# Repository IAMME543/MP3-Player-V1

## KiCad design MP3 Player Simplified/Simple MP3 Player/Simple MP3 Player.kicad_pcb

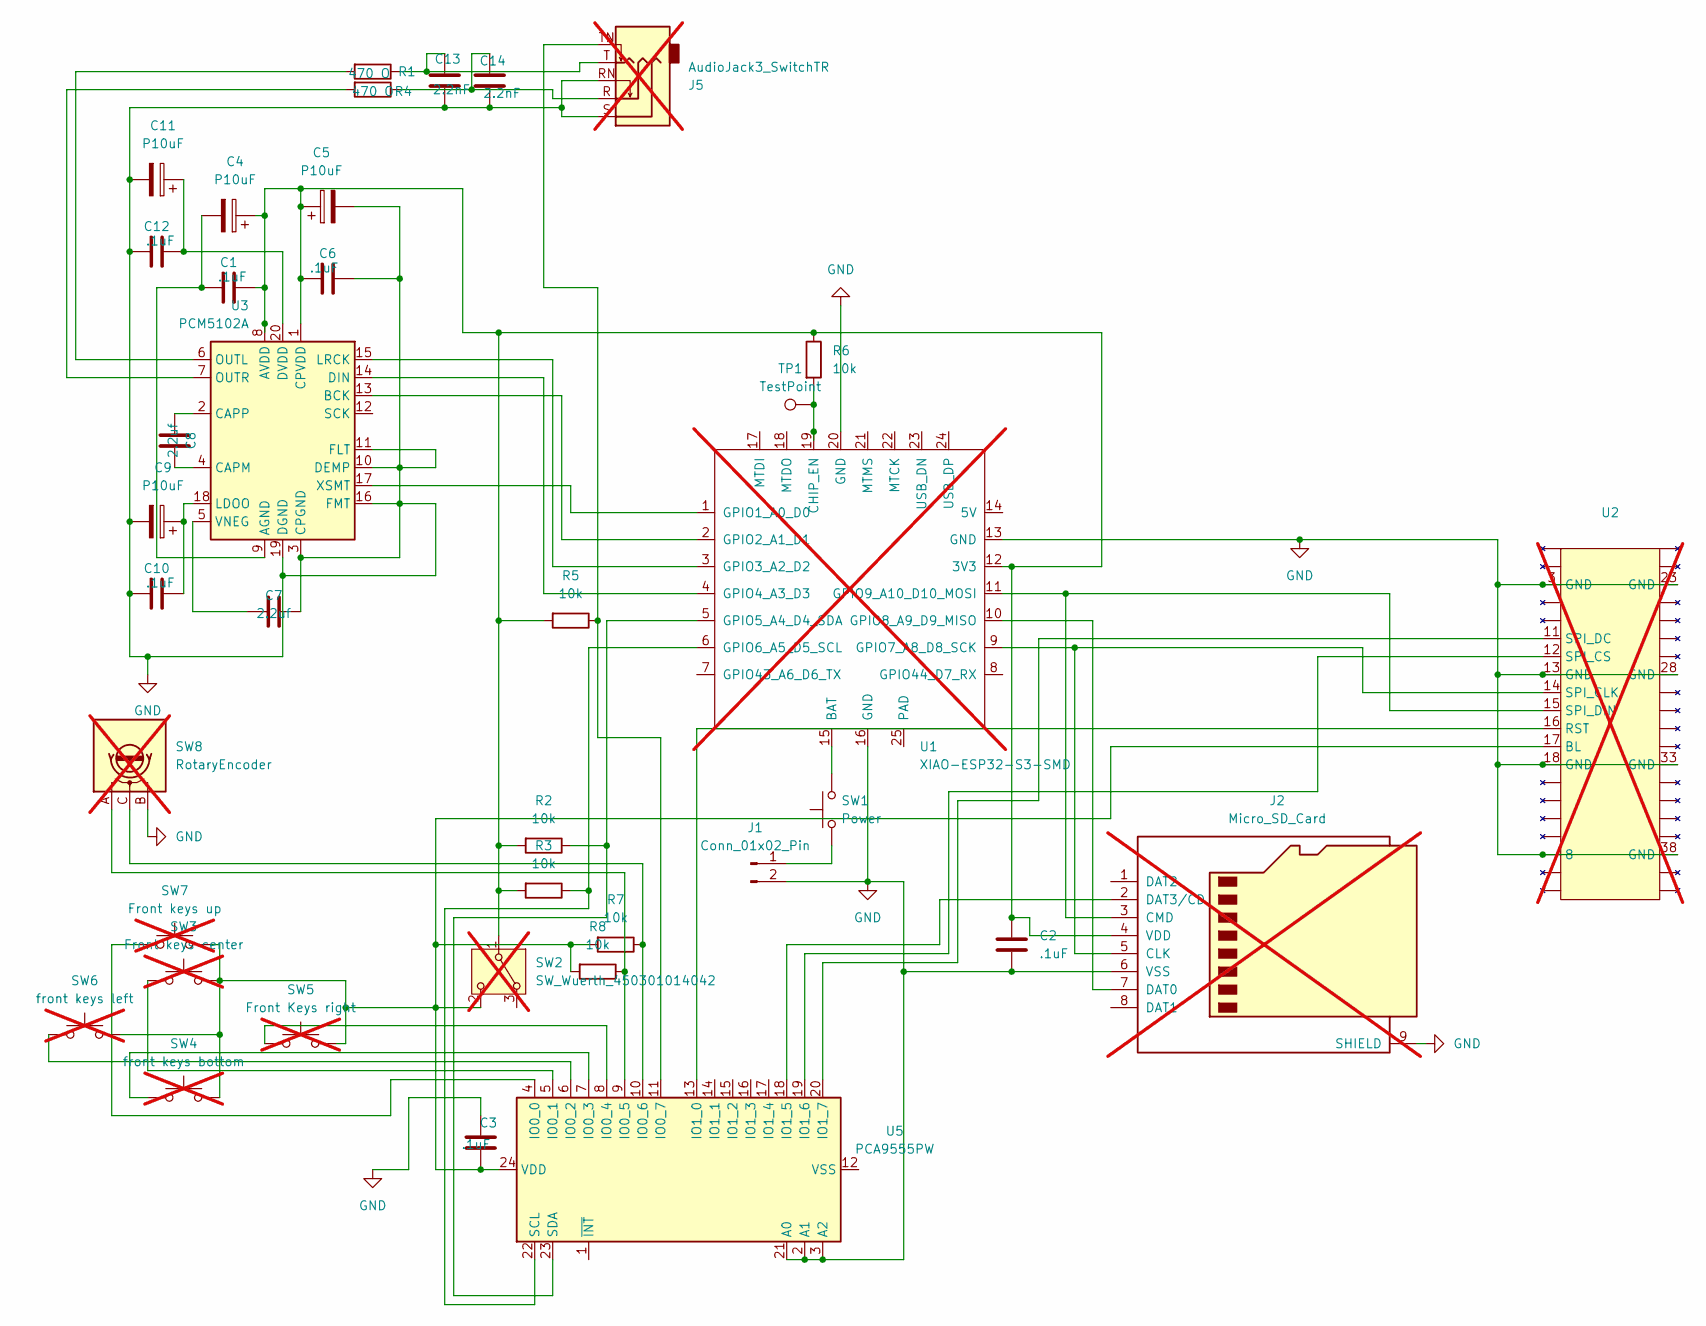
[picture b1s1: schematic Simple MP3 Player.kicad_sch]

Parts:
C1, C2, C3, C6, C10, C12: .1uF; C_0201_0603Metric
C4, C5, C9, C11: P10uF; CP_EIA-1608-08_AVX-J
C7, C8: 2.2uf; C_0201_0603Metric
C13, C14: 2.2nF; C_0201_0603Metric
J1: Conn_01x02_Pin; JST_PH_B2B-PH-K_1x02_P2.00mm_Vertical
J2: Micro_SD_Card; MicroSD Card; not fitted
J5: AudioJack3_SwitchTR; 3.5mm Audio Jack; not fitted
R1, R4: 470 O; R_0201_0603Metric
R2, R3, R5, R6, R7, R8: 10k; R_0201_0603Metric
SW1: Power; SW_Slide-03_Wuerth-WS-SLTV_10x2.5x6.4_P2.54mm
SW2: SW_Wuerth_450301014042; SW_Slide-03_Wuerth-WS-SLTV_10x2.5x6.4_P2.54mm; not fitted
SW3: Front keys center; SW_PUSH-12mm; not fitted
SW4: front keys bottom; SW_PUSH-12mm; not fitted
SW5: Front Keys right; SW_PUSH-12mm; not fitted
SW6: front keys left; SW_PUSH-12mm; not fitted
SW7: Front keys up; SW_PUSH-12mm; not fitted
SW8: RotaryEncoder; RE130F41175F12P; not fitted
TP1: TestPoint
U1: XIAO-ESP32-S3-SMD; XIAO-ESP32C3-SMD; not fitted
U2: Waveshare Pico LCD 2; not fitted
U3: PCM5102A; TSSOP-20_4.4x6.5mm_P0.65mm
U5: PCA9555PW; TSSOP-24_4.4x7.8mm_P0.65mm

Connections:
GND: C2.2, C3.1, C5.2, C6.1, C7.2, C9.2, C10.1, C11.2, C12.1, C13.2, C14.2, J1.2, J2.6 (VSS), J2.9 (SHIELD), J5.RN, J5.S, SW8.B, U1.13 (GND), U1.16 (GND), U1.20 (GND), U2., U2.3 (GND), U2.13 (GND), U2.18 (GND), U2.23 (GND), U2.28 (GND), U2.33 (GND), U2.38 (GND), U3.3 (CPGND), U3.10 (DEMP), U3.11 (FLT), U3.16 (FMT), U3.19 (DGND), U5.2 (A1), U5.3 (A2), U5.21 (A0)
unnamed: C13.1, J5.T, R1.1
unnamed: C14.1, J5.R, R4.1
unnamed: J1.1, SW1.1
unnamed: J2.5 (CLK), U1.9 (GPIO7_A8_D8_SCK), U2.14 (SPI_CLK)
unnamed: J2.3 (CMD), U1.11 (GPIO9_A10_D10_MOSI), U2.15 (SPI_DIN)
unnamed: J2.7 (DAT0), U1.10 (GPIO8_A9_D9_MISO)
unnamed: J2.2 (DAT3/CD), U5.18 (IO1_5)
unnamed: C1.2, C2.1, C4.1, C5.1, C6.2, J2.4 (VDD), R2.2, R3.2, R5.2, R6.1, SW2.1 (B), U1.12 (3V3), U3.1 (CPVDD), U3.8 (AVDD)
unnamed: C3.2, R7.2, R8.2, SW2.2 (C), SW3.2, SW4.2, SW5.2, SW6.2, SW7.2, U2.17 (BL), U5.24 (VDD)
unnamed: SW1.2, U1.15 (BAT)
unnamed: R6.2, TP1.1, U1.19 (CHIP_EN)
unnamed: U1.1 (GPIO1_A0_D0), U3.17 (XSMT)
unnamed: U1.2 (GPIO2_A1_D1), U3.13 (BCK)
unnamed: U1.3 (GPIO3_A2_D2), U3.15 (LRCK)
unnamed: U1.4 (GPIO4_A3_D3), U3.14 (DIN)
unnamed: R2.1, U1.5 (GPIO5_A4_D4_SDA), U5.23 (SDA)
unnamed: R3.1, U1.6 (GPIO6_A5_D5_SCL), U5.22 (SCL)
unnamed: U2.16 (RST), U5.13 (IO1_0)
unnamed: U2.12 (SPI_CS), U5.19 (IO1_6)
unnamed: U2.11 (SPI_DC), U5.20 (IO1_7)
unnamed: C1.1, C4.2, U3.9 (AGND)
unnamed: C8.2, U3.4 (CAPM)
unnamed: C8.1, U3.2 (CAPP)
unnamed: C11.1, C12.2, U3.20 (DVDD)
unnamed: C9.1, C10.2, U3.18 (LDOO)
unnamed: R1.2, U3.6 (OUTL)
unnamed: R4.2, U3.7 (OUTR)
unnamed: C7.1, U3.5 (VNEG)
unnamed: SW7.1, U5.4 (IO0_0)
unnamed: SW3.1, U5.5 (IO0_1)
unnamed: SW6.1, U5.6 (IO0_2)
unnamed: SW4.1, U5.7 (IO0_3)
unnamed: SW5.1, U5.8 (IO0_4)
unnamed: R8.1, SW8.A, U5.9 (IO0_5)
unnamed: R7.1, SW8.C, U5.10 (IO0_6)
unnamed: J5.TN, R5.1, U5.11 (IO0_7)

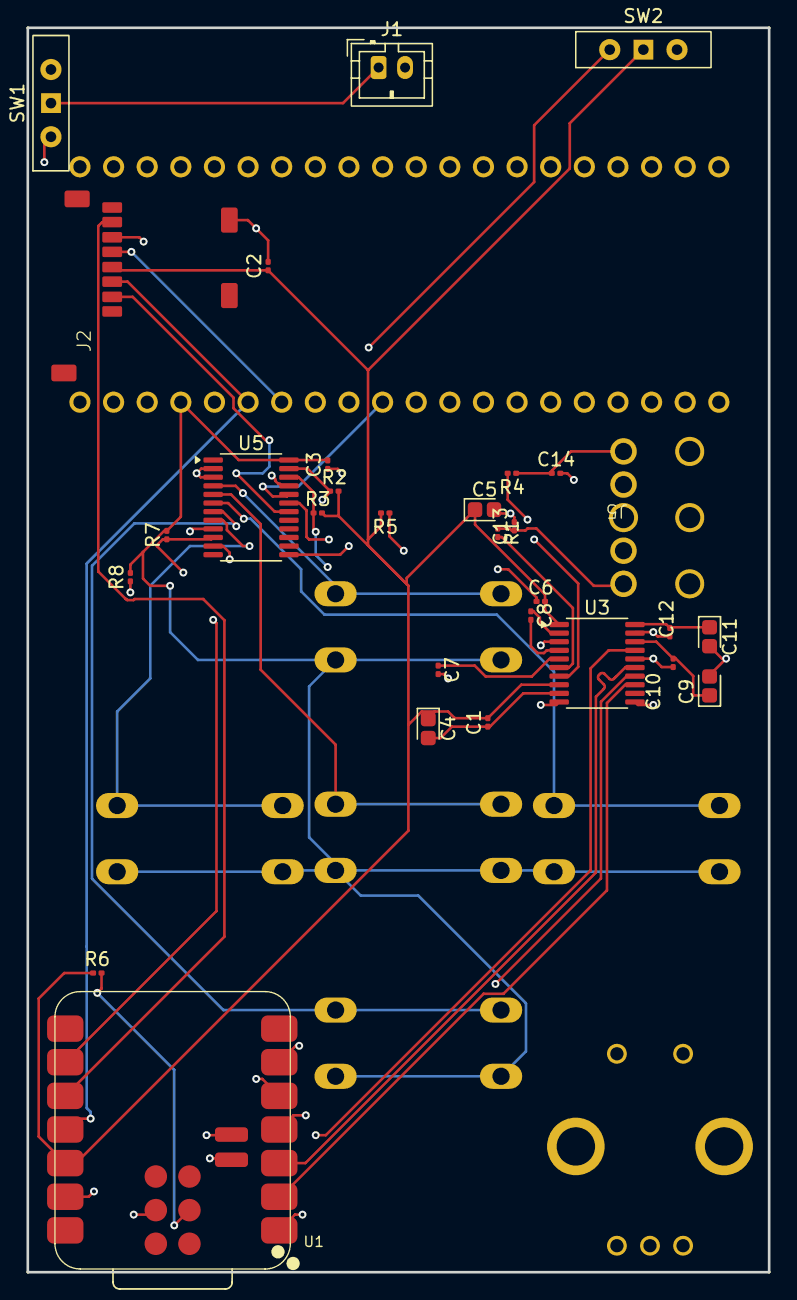
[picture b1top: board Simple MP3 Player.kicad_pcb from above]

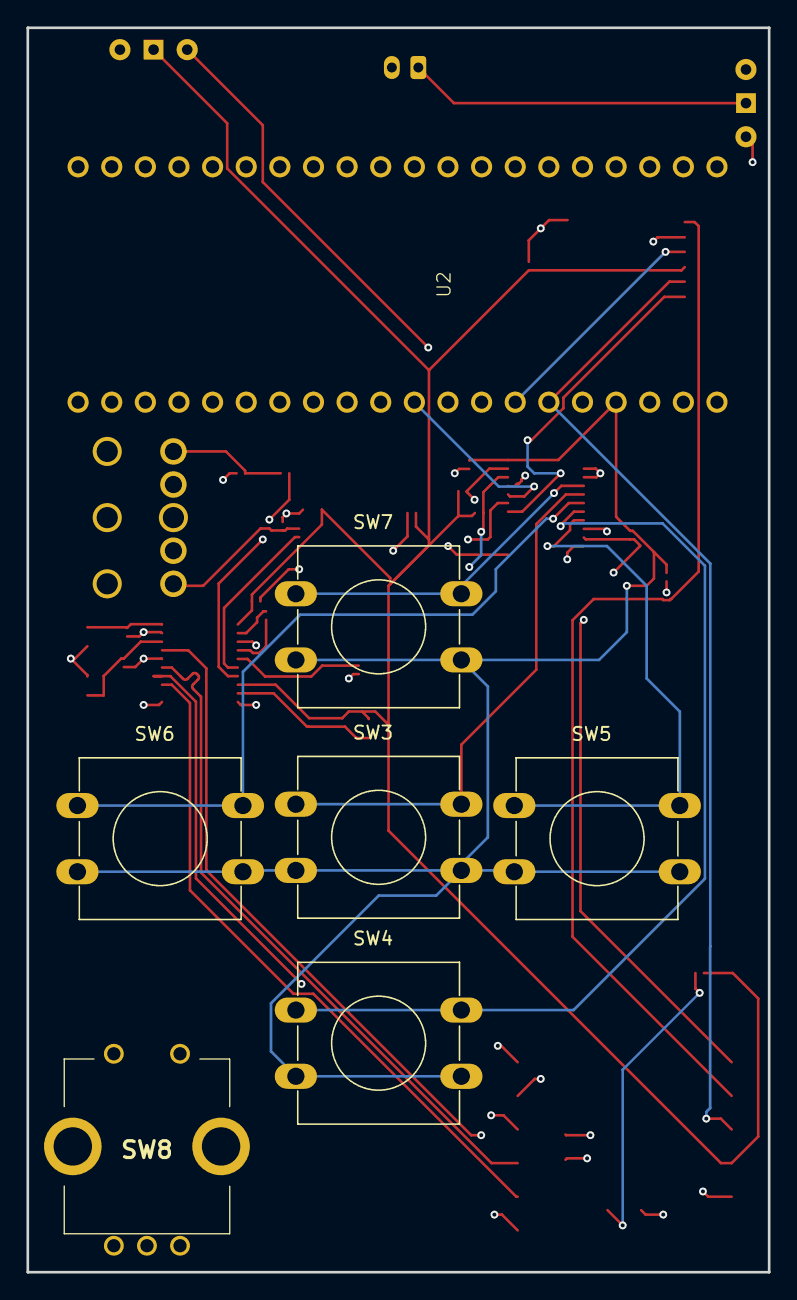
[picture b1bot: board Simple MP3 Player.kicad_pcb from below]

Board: 4 copper layers, 56.0 x 94.0 mm, 37 parts (7 on the bottom side), 37 nets.

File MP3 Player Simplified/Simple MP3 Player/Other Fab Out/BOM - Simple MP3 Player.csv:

Id;Designator;Footprint;Quantity;Designation;Supplier and ref;MPN;DNP
1;R7,R8,R6,R2,R3,R5;R_0201_0603Metric;6;10k;;;
2;U5;TSSOP-24_4.4x7.8mm_P0.65mm;1;PCA9555PW;;PCA9555PW;
3;SW2;SW_Slide-03_Wuerth-WS-SLTV_10x2.5x6.4_P2.54mm;1;SW_Wuerth_450301014042;;;DNP
4;C4,C9,C5,C11;CP_EIA-1608-08_AVX-J;4;P10uF;;;
5;C8,C7;C_0201_0603Metric;2;2.2uf;;;
6;C14,C13;C_0201_0603Metric;2;2.2nF;;;
7;U1;XIAO-ESP32C3-SMD;1;XIAO-ESP32-S3-SMD;;;DNP
8;C3,C12,C1,C6,C10,C2;C_0201_0603Metric;6;.1uF;;;
9;R1,R4;R_0201_0603Metric;2;470 O;;;
10;J5;3.5mm Audio Jack;1;AudioJack3_SwitchTR;;;DNP
11;SW1;SW_Slide-03_Wuerth-WS-SLTV_10x2.5x6.4_P2.54mm;1;Power;;;DNP
12;J2;MicroSD Card;1;Micro_SD_Card;;;DNP
13;U3;TSSOP-20_4.4x6.5mm_P0.65mm;1;PCM5102A;;PCM5102A;
14;J1;JST_PH_B2B-PH-K_1x02_P2.00mm_Vertical;1;Conn_01x02_Pin;;;DNP
15;SW7;SW_PUSH-12mm;1;Front keys up;;;DNP
16;U2;Waveshare Pico LCD 2;1;~;;;DNP
17;SW4;SW_PUSH-12mm;1;front keys bottom;;;DNP
18;SW3;SW_PUSH-12mm;1;Front keys center;;;DNP
19;SW8;RE130F41175F12P;1;RotaryEncoder;;;DNP
20;SW5;SW_PUSH-12mm;1;Front Keys right;;;DNP
21;SW6;SW_PUSH-12mm;1;front keys left;;;DNP

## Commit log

2026-03-24 added existing pcb design and chasis draft
2026-03-24 Layed out how micropython script will work
2026-03-29 created song album and artist and metadataparser class
2026-03-29 moved types to c
2026-03-29 switched to platformio
2026-04-19 boilerplate
2026-04-19 added notes for bodges
2026-04-30 lay out dispay and input cpp
2026-05-02 setup esp32 i2s audio library and move gpio library to pio
2026-05-02 discover get gpio expander state and lay out storage pins
